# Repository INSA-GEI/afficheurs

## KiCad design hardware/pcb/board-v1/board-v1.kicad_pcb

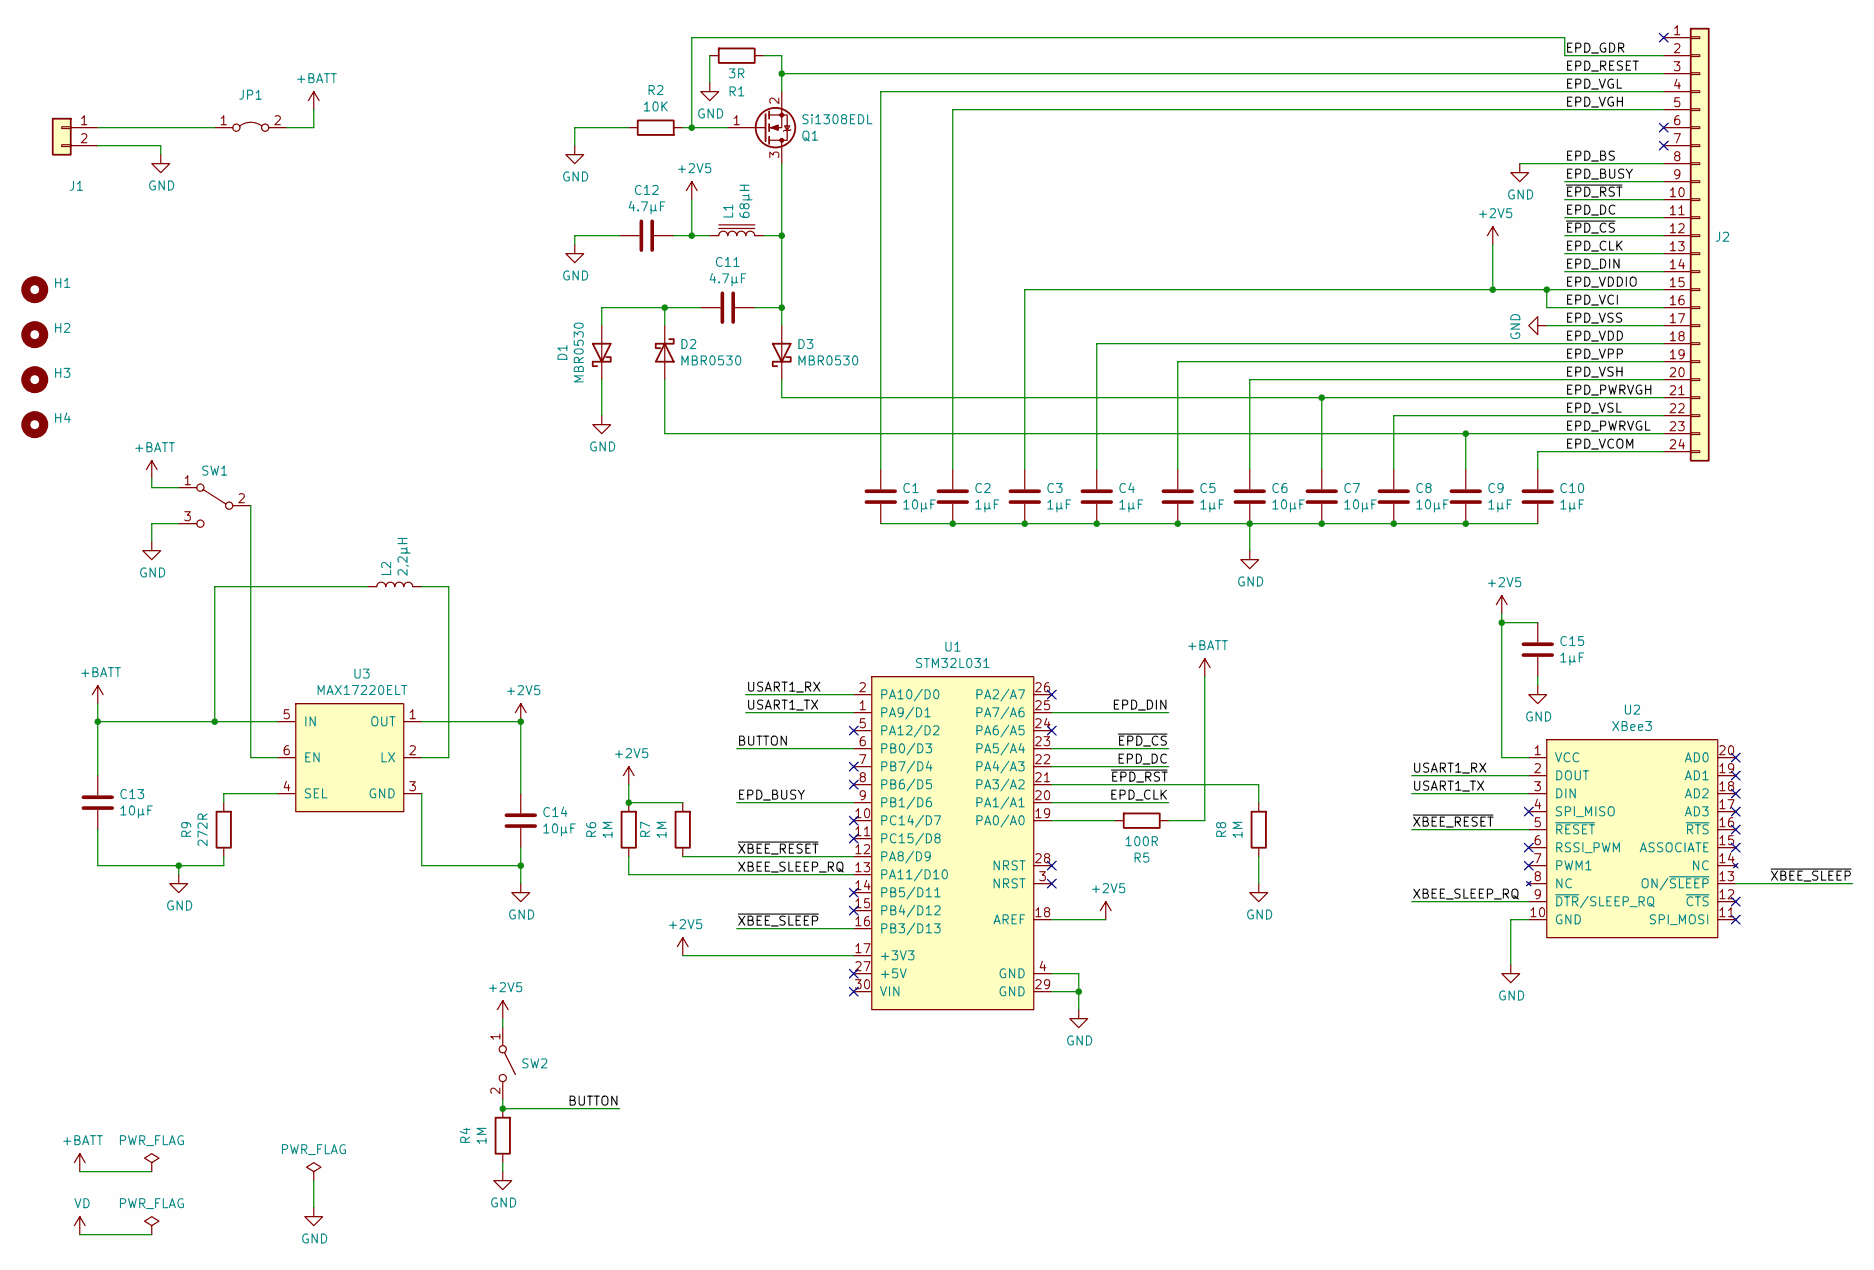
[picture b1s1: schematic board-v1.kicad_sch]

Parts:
C1, C6, C7, C8: 10µF; C_0603_1608Metric
C2, C3, C4, C5, C9, C10: 1µF; C_0603_1608Metric
C11, C12: 4.7µF; C_0603_1608Metric
C13, C14: 10µF; C_0805_2012Metric
C15: 1µF; C_0805_2012Metric
D1, D2, D3: MBR0530; D_TUMD2
H1, H2, H3, H4: MountingHole; MountingHole_3.2mm_M3
J1: Conn_01x02; PinHeader_1x02_P2.54mm_Vertical
J2: Conn_01x24; Hirose_FH12-24S-0.5SH_1x24-1MP_P0.50mm_Horizontal
JP1: Jumper_2_Bridged; SolderJumper-2_P1.3mm_Bridged_RoundedPad1.0x1.5mm
L1: 68µH; L_1210_3225Metric_Pad1.42x2.65mm_HandSolder
L2: 2,2µH; L_Wuerth_MAPI-4030
Q1: Si1308EDL; SOT-323_SC-70
R1: 3R; R_0603_1608Metric
R2: 10K; R_0603_1608Metric
R4, R6, R7, R8: 1M; R_0603_1608Metric
R5: 100R; R_0603_1608Metric
R9: 272R; R_0805_2012Metric
SW1: SW_SPDT; SW_Slide_1P2T_CK_OS102011MS2Q
SW2: SW_SPST; SW_Push_1P1T_NO_6x6mm_H9.5mm
U1: STM32L031; STM32-Nucleo-32
U2: XBee3; Xbee3
U3: MAX17220ELT; uDFN-6-1EP_2x2mm_P0.65mm_EP1x1.6mm

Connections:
+2V5: C3.1, C12.2, C14.1, C15.1, J2.15, J2.16, L1.1, R6.2, R7.2, SW2.1 (A), U1.17 (+3V3), U1.18 (AREF), U2.1 (VCC), U3.1 (OUT)
+BATT: C13.1, JP1.2 (B), L2.1, R5.1, SW1.1 (A), U3.5 (IN)
/BUTTON: R4.2, SW2.2 (B), U1.6 (PB0/D3)
/EPD_BUSY: J2.9, U1.9 (PB1/D6)
/EPD_CLK: J2.13, U1.20 (PA1/A1)
/EPD_DC: J2.11, U1.22 (PA4/A3)
/EPD_DIN: J2.14, U1.25 (PA7/A6)
/EPD_GDR: J2.2, Q1.1 (G), R2.2
/EPD_PWRVGH: C7.1, D3.1 (K), J2.21
/EPD_PWRVGL: C9.1, D2.2 (A), J2.23
/EPD_RESET: J2.3, Q1.2 (S), R1.1
/EPD_VCOM: C10.1, J2.24
/EPD_VDD: C4.1, J2.18
/EPD_VGH: C2.1, J2.5
/EPD_VGL: C1.1, J2.4
/EPD_VPP: C5.1, J2.19
/EPD_VSH: C6.1, J2.20
/EPD_VSL: C8.1, J2.22
/USART1_RX: U1.2 (PA10/D0), U2.2 (DOUT)
/USART1_TX: U1.1 (PA9/D1), U2.3 (DIN)
/XBEE_SLEEP_RQ: R6.1, U1.13 (PA11/D10), U2.9 (~DTR/SLEEP_RQ)
/~EPD_CS: J2.12, U1.23 (PA5/A4)
/~EPD_RST: J2.10, R8.2, U1.21 (PA3/A2)
/~XBEE_RESET: R7.1, U1.12 (PA8/D9), U2.5 (~RESET)
/~XBEE_SLEEP: U1.16 (PB3/D13), U2.13 (ON/~SLEEP)
GND: C1.2, C2.2, C3.2, C4.2, C5.2, C6.2, C7.2, C8.2, C9.2, C10.2, C12.1, C13.2, C14.2, C15.2, D1.1 (K), J1.2, J2.8, J2.17, R1.2, R2.1, R4.1, R8.1, R9.1, SW1.3 (C), U1.4 (GND), U1.29 (GND), U2.10 (GND), U3.3 (GND)
unnamed: C11.1, D1.2 (A), D2.1 (K)
unnamed: C11.2, D3.2 (A), L1.2, Q1.3 (D)
unnamed: J1.1, JP1.1 (A)
unnamed: L2.2, U3.2 (LX)
unnamed: R5.2, U1.19 (PA0/A0)
unnamed: R9.2, U3.4 (SEL)
unnamed: SW1.2 (B), U3.6 (EN)

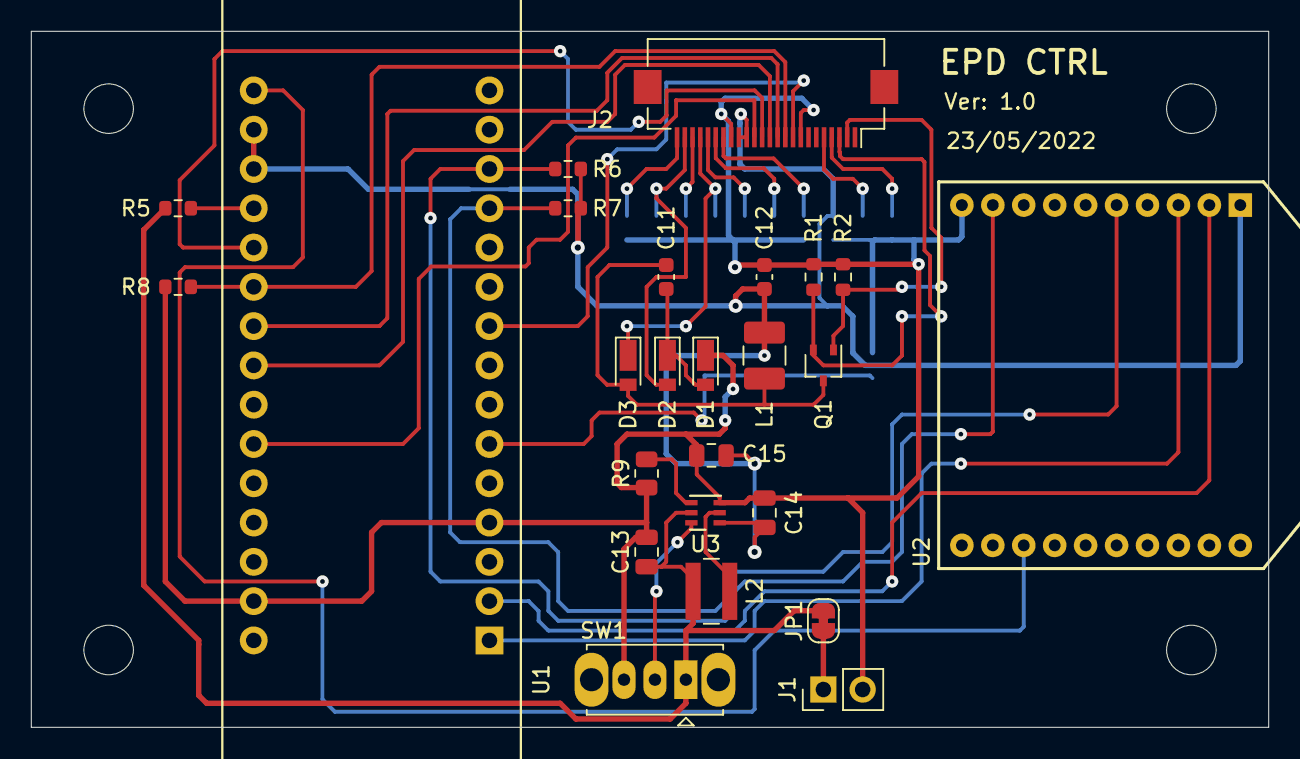
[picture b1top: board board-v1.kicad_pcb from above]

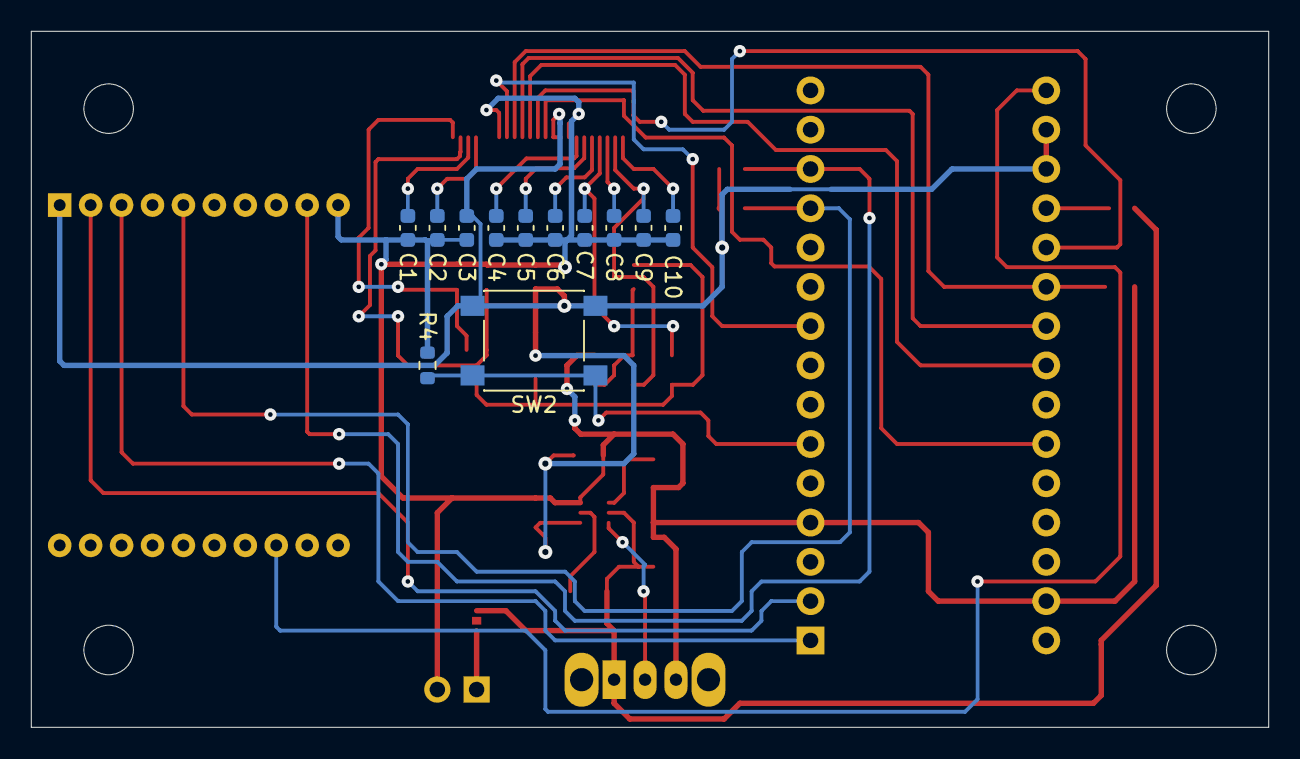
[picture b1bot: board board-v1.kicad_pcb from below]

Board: 2 copper layers, 80.0 x 45.0 mm, 41 parts (16 on the bottom side), 33 nets.

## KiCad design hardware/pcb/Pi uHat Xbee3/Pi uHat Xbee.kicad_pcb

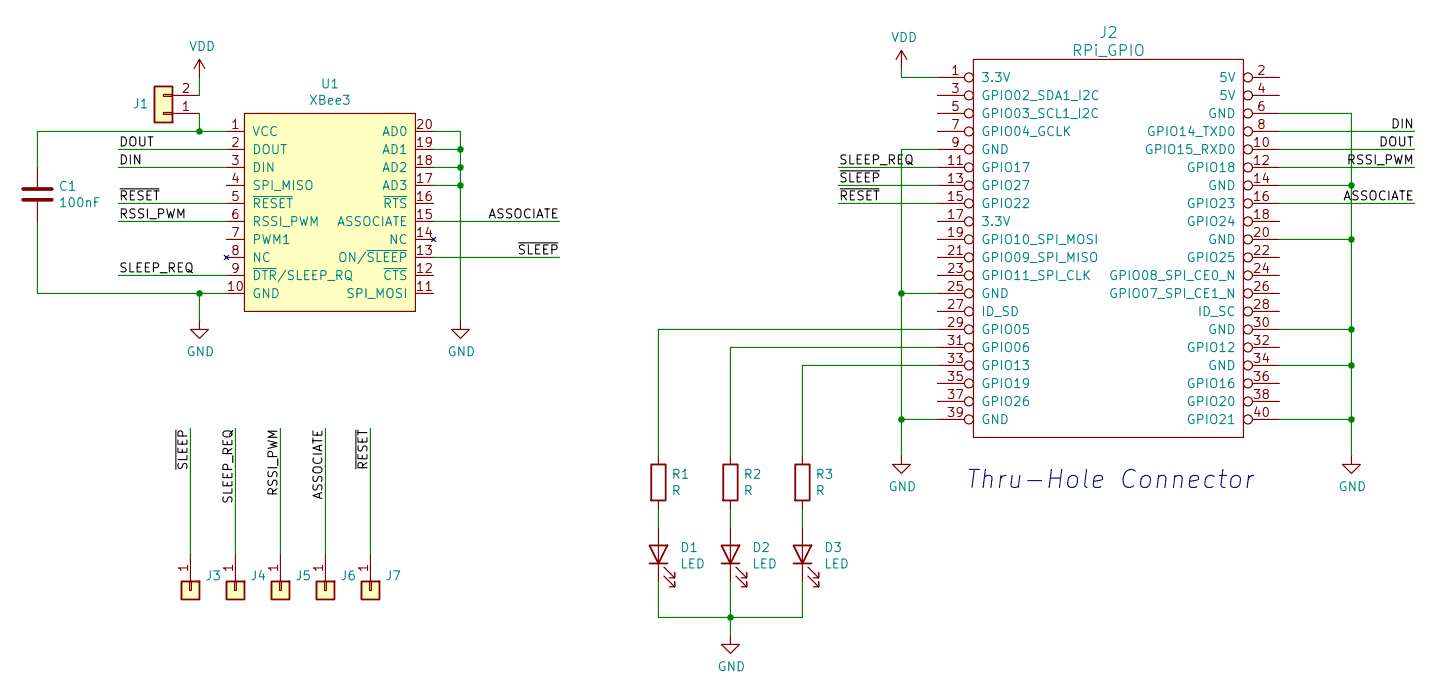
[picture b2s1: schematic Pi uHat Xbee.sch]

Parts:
C1: 100nF; C_1206_3216Metric_Pad1.33x1.80mm_HandSolder
D1, D2, D3: LED; LED_1206_3216Metric_Pad1.42x1.75mm_HandSolder
J1: Conn_01x02; PinHeader_1x02_P2.54mm_Vertical
J2: RPi_GPIO; PinHeader_2x20_P2.54mm_Vertical
J3, J4, J5, J6, J7: Conn_01x01; PinHeader_1x01_P2.54mm_Vertical
R1, R2, R3: R; R_1206_3216Metric_Pad1.30x1.75mm_HandSolder
U1: XBee3; Xbee3

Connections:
/ASSOCIATE: J2.16 (GPIO23), J6.1, U1.15 (ASSOCIATE)
/DIN: J2.8 (GPIO14_TXD0), U1.3 (DIN)
/DOUT: J2.10 (GPIO15_RXD0), U1.2 (DOUT)
/RSSI_PWM: J2.12 (GPIO18), J5.1, U1.6 (RSSI_PWM)
/SLEEP_REQ: J2.11 (GPIO17), J4.1, U1.9 (~DTR~/SLEEP_RQ)
/~RESET: J2.15 (GPIO22), J7.1, U1.5 (~RESET)
/~SLEEP: J2.13 (GPIO27), J3.1, U1.13 (ON/~SLEEP)
GND: C1.2, D1.1 (K), D2.1 (K), D3.1 (K), J2.6 (GND), J2.9 (GND), J2.14 (GND), J2.20 (GND), J2.25 (GND), J2.30 (GND), J2.34 (GND), J2.39 (GND), J2.40 (GPIO21), U1.10 (GND), U1.17 (AD3), U1.18 (AD2), U1.19 (AD1), U1.20 (AD0)
unnamed: C1.1, J1.1, U1.1 (VCC)
unnamed: D1.2 (A), R1.2
unnamed: D2.2 (A), R2.2
unnamed: D3.2 (A), R3.2
unnamed: J2.29 (GPIO05), R1.1
unnamed: J2.31 (GPIO06), R2.1
unnamed: J2.33 (GPIO13), R3.1
VDD: J1.2, J2.1 (3.3V)

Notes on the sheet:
Thru-Hole Connector

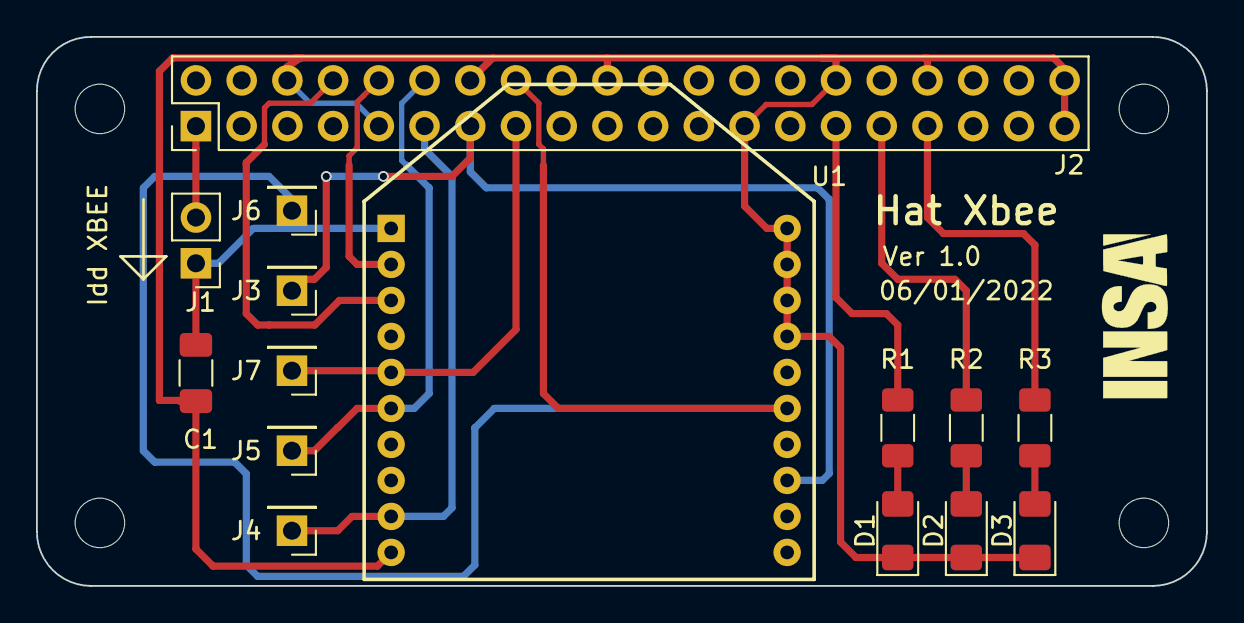
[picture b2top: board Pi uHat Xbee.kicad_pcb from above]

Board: 2 copper layers, 65.0 x 30.5 mm, 15 parts (0 on the bottom side), 16 nets.

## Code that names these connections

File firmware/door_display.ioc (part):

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Mcu.Name=STM32L432K(B-C)Ux
Mcu.Package=UFQFPN32
Mcu.UserName=STM32L432KCUx
PA0.Signal=ADCx_IN5
PA1.Mode=Simplex_Bidirectional_Master
PA1.Signal=SPI1_SCK
PA10.Mode=Asynchronous
PA10.Signal=USART1_RX
PA11.GPIOParameters=GPIO_Label
PA11.GPIO_Label=XBEE_SLEEP_RQ
PA11.Signal=GPIO_Output
PA13\ (JTMS-SWDIO).GPIOParameters=GPIO_Label
PA13\ (JTMS-SWDIO).GPIO_Label=SWDIO
PA13\ (JTMS-SWDIO).Mode=Serial_Wire
PA13\ (JTMS-SWDIO).Signal=SYS_JTMS-SWDIO
PA14\ (JTCK-SWCLK).GPIOParameters=GPIO_Label
PA14\ (JTCK-SWCLK).GPIO_Label=SWCLK
PA14\ (JTCK-SWCLK).Mode=Serial_Wire
PA14\ (JTCK-SWCLK).Signal=SYS_JTCK-SWCLK
PA15\ (JTDI).GPIOParameters=GPIO_Label
PA15\ (JTDI).GPIO_Label=VCP_RX
PA15\ (JTDI).Mode=Asynchronous
PA15\ (JTDI).Signal=USART2_RX
PA2.GPIOParameters=GPIO_Label
PA2.GPIO_Label=VCP_TX
PA2.Mode=Asynchronous
PA2.Signal=USART2_TX
PA3.GPIOParameters=GPIO_Label
PA3.GPIO_Label=RST
PA3.Signal=GPIO_Output
PA4.GPIOParameters=GPIO_Label
PA4.GPIO_Label=DC
PA4.Signal=GPIO_Output
PA5.GPIOParameters=PinState,GPIO_Label
PA5.GPIO_Label=SPI_CS
PA5.PinState=GPIO_PIN_SET
PA5.Signal=GPIO_Output
PA7.Mode=Simplex_Bidirectional_Master
PA7.Signal=SPI1_MOSI
PA8.GPIOParameters=GPIO_Label
PA8.GPIO_Label=XBEE_RESET
PA8.Signal=GPIO_Output
PA9.Mode=Asynchronous
PA9.Signal=USART1_TX
PB0.GPIOParameters=GPIO_Label
PB0.GPIO_Label=BUTTON
PB0.Signal=GPXTI0
PB1.GPIOParameters=GPIO_Label
PB1.GPIO_Label=BUSY
PB1.Signal=GPXTI1
PB3\ (JTDO-TRACESWO).GPIOParameters=GPIO_Label
PB3\ (JTDO-TRACESWO).GPIO_Label=XBEE_SLEEP
PB3\ (JTDO-TRACESWO).Signal=GPXTI3
PC14-OSC32_IN\ (PC14).Mode=LSE-External-Oscillator
PC14-OSC32_IN\ (PC14).Signal=RCC_OSC32_IN
PC15-OSC32_OUT\ (PC15).Mode=LSE-External-Oscillator
PC15-OSC32_OUT\ (PC15).Signal=RCC_OSC32_OUT
RCC.HSE_VALUE=8000000
RCC.SYSCLKFreq_VALUE=64000000
RCC.SYSCLKSource=RCC_SYSCLKSOURCE_PLLCLK
board=NUCLEO-L432KC
boardIOC=true

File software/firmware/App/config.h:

/*
 * config.h
 *
 *  Created on: 27 avr. 2022
 *      Author: dimercur
 */

#ifndef CONFIG_H_
#define CONFIG_H_

#include "stm32l4xx_hal.h"
#include "cmsis_os.h"

void Error_Handler(void);

TickType_t msToTicks(TickType_t ms);

#define VCP_TX_Pin 					GPIO_PIN_2
#define VCP_TX_GPIO_Port 			GPIOA

#define VCP_RX_Pin 					GPIO_PIN_15
#define VCP_RX_GPIO_Port 			GPIOA

#define RST_Pin 					GPIO_PIN_3
#define RST_GPIO_Port 				GPIOA

#define DC_Pin 						GPIO_PIN_4
#define DC_GPIO_Port 				GPIOA

#define SPI_CS_Pin 					GPIO_PIN_5
#define SPI_CS_GPIO_Port 			GPIOA

#define SPI_MISO_Pin 				GPIO_PIN_1
#define SPI_MISO_GPIO_Port 			GPIOA

#define SPI_MOSI_Pin 				GPIO_PIN_7
#define SPI_MOSI_GPIO_Port 			GPIOA

#define BUSY_Pin 					GPIO_PIN_1
#define BUSY_GPIO_Port 				GPIOB
#define BUSY_EXTI_IRQn 				EXTI1_IRQn

#define BUTTON_Pin 					GPIO_PIN_0
#define BUTTON_GPIO_Port 			GPIOB
#define BUTTON_EXTI_IRQn 			EXTI0_IRQn

#define XBEE_RESET_Pin 				GPIO_PIN_8
#define XBEE_RESET_GPIO_Port 		GPIOA

#define XBEE_SLEEP_RQ_Pin 			GPIO_PIN_11
#define XBEE_SLEEP_RQ_GPIO_Port	 	GPIOA

#define XBEE_SLEEP_Pin 				GPIO_PIN_3
#define XBEE_SLEEP_GPIO_Port 		GPIOB
#define XBEE_SLEEP_EXTI_IRQn 		EXTI3_IRQn

#define SWDIO_Pin 					GPIO_PIN_13
#define SWDIO_GPIO_Port 			GPIOA

#define SWCLK_Pin 					GPIO_PIN_14
#define SWCLK_GPIO_Port 			GPIOA

/**
 * e-Paper GPIO
 **/
#define EPD_RST_PIN     			RST_GPIO_Port, RST_Pin
#define EPD_DC_PIN      			DC_GPIO_Port, DC_Pin
#define EPD_CS_PIN      			SPI_CS_GPIO_Port, SPI_CS_Pin
#define EPD_BUSY_PIN    			BUSY_GPIO_Port, BUSY_Pin

#define STACK_SIZE 					200

#define PriorityInit    			        (configMAX_PRIORITIES -1)
#define PriorityWakeUpRTC        	        (configMAX_PRIORITIES -4)
#define PriorityWakeUpButton	            (configMAX_PRIORITIES -5)
#define PriorityFirstWakeUp	                (configMAX_PRIORITIES -2)
#define PriorityFirstWakeUpOfTheDay	        (configMAX_PRIORITIES -3)

#define EPD_CONFIG_LUT				1

#define DEBUG_PROTOCOL				1
#define DEBUG_CHANNEL				0x12
#define DEBUG_PANID					0x0000
#define DEBUG_PROTOCOL_TIMEOUT	    2000 // Timeout of around 2s

#define DEBUG_PROTOCOL_FAKE_CONFIG  0
#define PANID_COMMAND_STRING		"ATID=DEAD\r"
#define PANID                       0xDEAD
#define DEVICE_UID_TEST             0x1B00
#define DEFAULT_TIME                1000 //MARCHE PAS
#define DEFAULT_DAY                 01 //01 MONDAY

#define ZIGBEE_SERVER_ADDR			0

void DEBUG_Init(void);
void DEBUG_StartTimeMeasure(void);
uint32_t DEBUG_EndTimeMeasure(void);

#endif /* CONFIG_H_ */

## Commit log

2021-02-03 repository init
2021-12-10 l'ecran fonctionne
2021-12-14 Reorganisation repertoire + portage des fonts sur systeme lvgl
2021-12-14 Ajout d'icone, suppression de fichiers inutile
2021-12-14 Agrandissement de l'espace entre caracter de 1 pixel à 2
2022-01-05 ajout de la carte d'evaluation
2022-01-05 etape intermediaire
2022-01-06 Carte eval finie
2022-01-06 Hat Pi Wbee fini
2022-01-10 correction d'un bug dans la gestion des report
2022-01-21 reorganisation de l'arborescence + renommage serveré
2022-01-24 evolution en cours
2022-01-31 reprise du code, ajout de la gestion reseau des gateways
2022-02-04 Ajout d'une machine a etat dans le serveur
2022-02-11 evolutions
2022-02-15 evolution de la classe decoded_frame en multiple classe, chacune pour un message
2022-02-16 ajout de la class networkmgr et messages, a debugger
2022-02-18 Simplification du systeme des messages
2022-03-03 Point d'etape developpement gateway
2022-03-03 Premiere version fonctionnelle de la gateway. Besoin de rajouter le support des commandes AT pour la configuration du Xbee
2022-03-03 Gestion des commandes AT en cours
2022-03-07 Commandes AT fonctionnent
2022-03-08 Gateway complete, à tester sur RPI
2022-03-28 Basculement sur la methode getEvents plutot que getactivities pour la recuperation du calendrier
2022-03-30 Recuperation des infos ADE et tri OK
2022-03-30 Ajout d'un systeme de dictionnaire + nettoyage de code
2022-03-30 serveur reseau grossierement réalisé
2022-03-30 Classe messagemgr et class message faites, actionhandler debuté, a finir
2022-03-31 reponses aux commande a peu pres correctes, reste le timer pour la commande JOIN
2022-04-04 Version de gateway et de server suffisament fonctionnels pour etre utilisés
2022-04-06 Debug driver XBEE
2022-04-12 Driver xbee a peu pres ok
2022-04-15 Timeout ajouté dans xbee_ll, scan de canaux et connection au reseau OK
2022-04-20 preparation du test pour la recuperation des calendriers
2022-04-25 Recuperation de calendrier OK, timeout a rajouter, et verifier les strncpy (à remplacer par memcpy)
2022-04-26 debut travaux sur l'ecran
2022-04-27 Ecrans fonctionnels
2022-04-29 ajout des drivers adc, exti et rtc, a debugger
2022-05-02 debut du passage sous freertos
2022-05-04 demarrage du port sous freertos
2022-05-06 Passage sous Freertos pour battery,rtc et button
2022-05-11 Tous les drivers sont passé au format freertos, mais l'ecran ne marche plus et le Xbee n'est pas testé. Les autres peripheriques semblent marcher
2022-05-12 Afficheur OK
2022-05-13 xbee marche, ecran marche, affiche des premieres infos
2022-05-19 Soft porté sous freertos, focntion d'effacement d'ecran accelerée x7
2023-01-09 dernier commit avant changement de branche
2023-06-05 ajout bidon pour remonter sur depot
2023-06-07 Modif version1
2023-06-07 Version 2
2023-06-14 Xbee marche en TX mais pas en RX lorsque le module passe en mode API
2023-06-14 Correction de la reception XBEE, mais probleme d'optimisation, notamment sur les baudrate à partir de 115200 bauds
2023-06-14 Changement dans le fonctionnement RX de l'UART XBEE: mode IT en continu, et stockage des donnée uniquement si le besoin est necessaire. Permet de monter à 115200 bauds mais pas au dessus (???)
2023-11-24 Fin de stage
2023-11-24 commit avant merge
2023-11-24 Nettoyage de l'arboresence avant debut des travaux
2023-11-28 Transfert de la consultation depuis l'API ADE vers des scripts CSN
2023-12-08 Gros evolution, separation par classe, partie ADE bien avancée mais zigbee a faire entierement
2023-12-11 Prise en charge des commandes Zigbee partielle
2023-12-12 serveur fonctionnel, a debugger desormais et rendre plus fiable
